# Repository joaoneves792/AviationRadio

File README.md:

# AviationRadio
Aviation inspired radio using an Arduino + Si4844

It can receive broadcast FM and VHF AM, including the civil aviation airband, (using a downconverter based on SA612 + Si5351)

It also works as a flight sim peripheral, currently with an X-Plane 11 plugin (Linux only) for controlling the plane radios.

# TODO 
- documentation
- BOM
- Redesign the 3D printed box (current printed version is very rough quality)

# Initial working prototype pictures

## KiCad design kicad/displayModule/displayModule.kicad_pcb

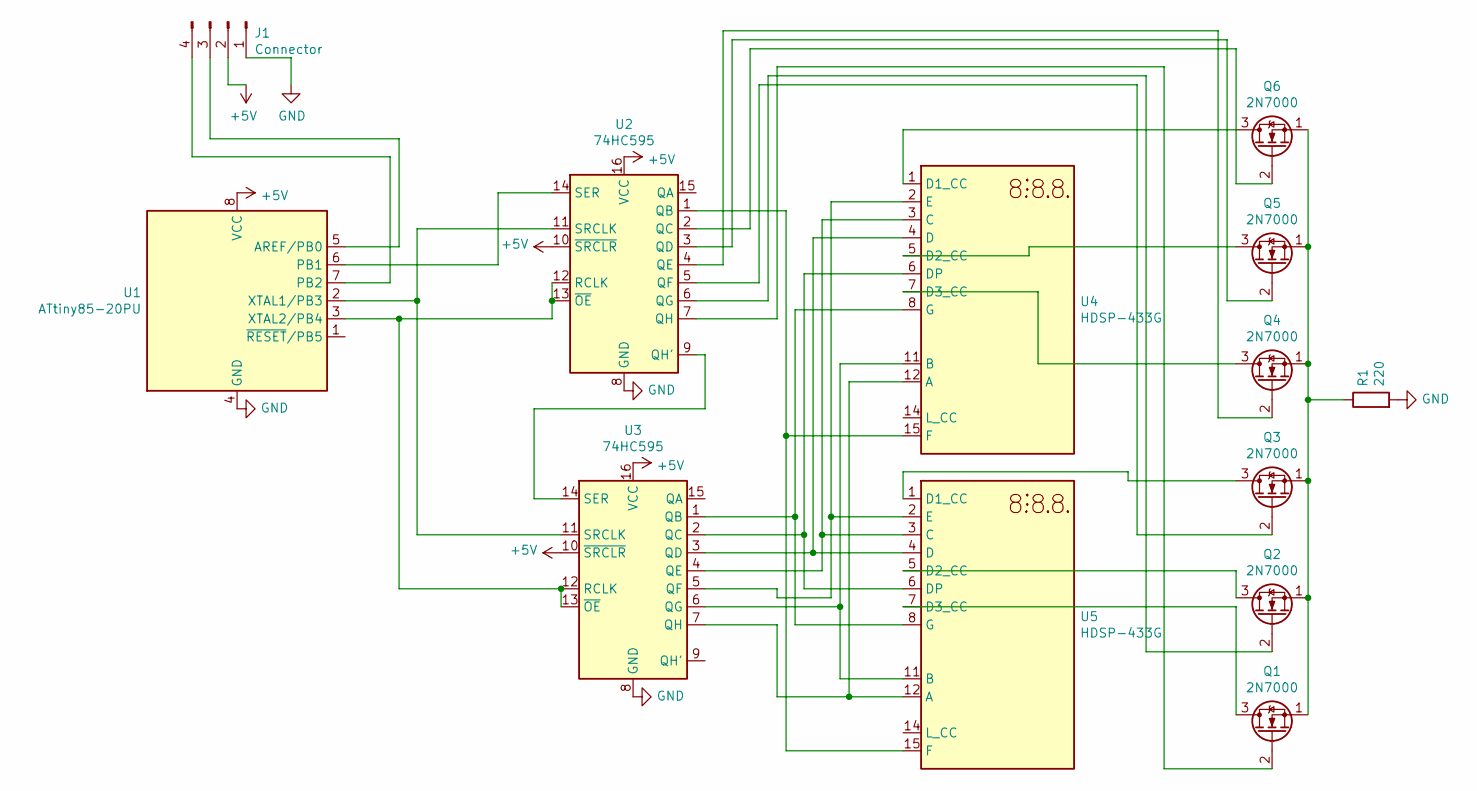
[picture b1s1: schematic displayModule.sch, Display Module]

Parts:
J1: Connector; PinHeader_1x04_P2.54mm_Vertical
Q1, Q2, Q3, Q4, Q5, Q6: 2N7000; TO-92_Inline_Wide
R1: 220; R_Axial_DIN0207_L6.3mm_D2.5mm_P7.62mm_Horizontal
U1: ATtiny85-20PU; DIP-8_W7.62mm
U2, U3: 74HC595; DIP-16_W7.62mm
U4, U5: HDSP-433G

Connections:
+5V: J1.2, U1.8 (VCC), U2.10 (~SRCLR), U2.16 (VCC), U3.10 (~SRCLR), U3.16 (VCC)
GND: J1.1, R1.2, U1.4 (GND), U2.8 (GND), U3.8 (GND)
unnamed: J1.3, U1.5 (AREF/PB0)
unnamed: J1.4, U1.7 (PB2)
unnamed: Q1.1 (S), Q2.1 (S), Q3.1 (S), Q4.1 (S), Q5.1 (S), Q6.1 (S), R1.1
unnamed: Q1.2 (G), U2.7 (QH)
unnamed: Q1.3 (D), U5.7 (D3_CC)
unnamed: Q2.2 (G), U2.6 (QG)
unnamed: Q2.3 (D), U5.5 (D2_CC)
unnamed: Q3.2 (G), U2.5 (QF)
unnamed: Q3.3 (D), U5.1 (D1_CC)
unnamed: Q4.2 (G), U2.4 (QE)
unnamed: Q4.3 (D), U4.7 (D3_CC)
unnamed: Q5.2 (G), U2.3 (QD)
unnamed: Q5.3 (D), U4.5 (D2_CC)
unnamed: Q6.2 (G), U2.2 (QC)
unnamed: Q6.3 (D), U4.1 (D1_CC)
unnamed: U1.2 (XTAL1/PB3), U2.11 (SRCLK), U3.11 (SRCLK)
unnamed: U1.3 (XTAL2/PB4), U2.12 (RCLK), U2.13 (~OE), U3.12 (RCLK), U3.13 (~OE)
unnamed: U1.6 (PB1), U2.14 (SER)
unnamed: U2.1 (QB), U4.15 (F), U5.15 (F)
unnamed: U2.9 (QH'), U3.14 (SER)
unnamed: U3.1 (QB), U4.8 (G), U5.8 (G)
unnamed: U3.2 (QC), U4.6 (DP), U5.6 (DP)
unnamed: U3.3 (QD), U4.4 (D), U5.4 (D)
unnamed: U3.4 (QE), U4.3 (C), U5.3 (C)
unnamed: U3.5 (QF), U4.2 (E), U5.2 (E)
unnamed: U3.6 (QG), U4.11 (B), U5.11 (B)
unnamed: U3.7 (QH), U4.12 (A), U5.12 (A)

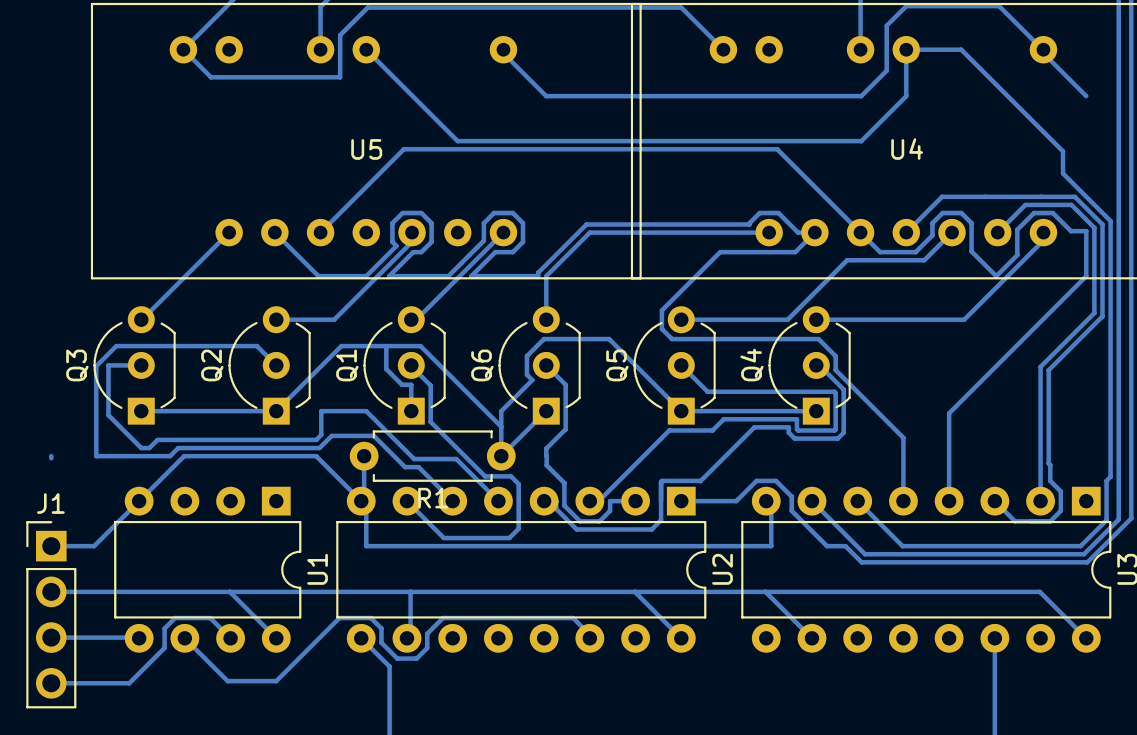
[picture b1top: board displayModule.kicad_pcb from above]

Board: 2 copper layers, 13 parts (0 on the bottom side), 29 nets.

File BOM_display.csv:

Name	Type	Value	Quantity	Unit Price	Quant Price		Total BOM Cost
Q1, Q2, Q3, Q4, Q5, Q6	TO92	2N7000	6	0,10 ?	0,60 ?		11,19 ?
IC3	DIP8	ATTiny85	1	2,68 ?	2,68 ?		
Connector1	Connector: Pin Strip (100 mil) (4 pins)	Connector1	1	0,10 ?	0,10 ?		
R1	AngledResistor	220	1	0,02 ?	0,02 ?		
IC1, IC2	DIP16	74HC595	2	0,71 ?	1,42 ?		
7S1, 7S2	7SEG	HDSP-433G	2	2,60 ?	5,20 ?		
Board	PerfBoard	PerfBoard	1	1,17 ?	1,17 ?

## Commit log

2021-01-11 Added fritzing drafts
2021-01-31 working ASM ATtiny code
2021-01-31 Fixed swapped displays
2021-02-12 Added 3dprints and exposing nano every clock to ATDD
2021-02-16 working FM radio
2021-02-16 3d models for working radio
2021-02-17 volume pot
2021-03-09 soldering radio
2021-03-09 Attempting to get clock to work
2021-03-22 properties queue
2021-04-12 working with XPLANE11
2021-05-31 First commit with working Airband support
2021-06-01 Fixed some bugs
2021-06-01 fixed tuning of LO
2021-06-01 Added initial prototype pictures
2021-06-01 Repo cleanup
2021-06-02 cleaned up veroroute designs
2021-06-13 tuned squelch settings
2021-07-11 testing BL
2021-07-11 BL perfboard
2021-07-21 Added schematics for amplifier and main radio circuits
2021-07-21 Added schematics for displays and downconverter
2021-07-22 improved radio and amplifier schematic
2021-07-24 Power supply modifications
2021-07-30 Begin work on display module printed pcb order
2021-09-10 Only activate squelch after AM transmission is picked up
2021-10-23 Fixed volume handling
